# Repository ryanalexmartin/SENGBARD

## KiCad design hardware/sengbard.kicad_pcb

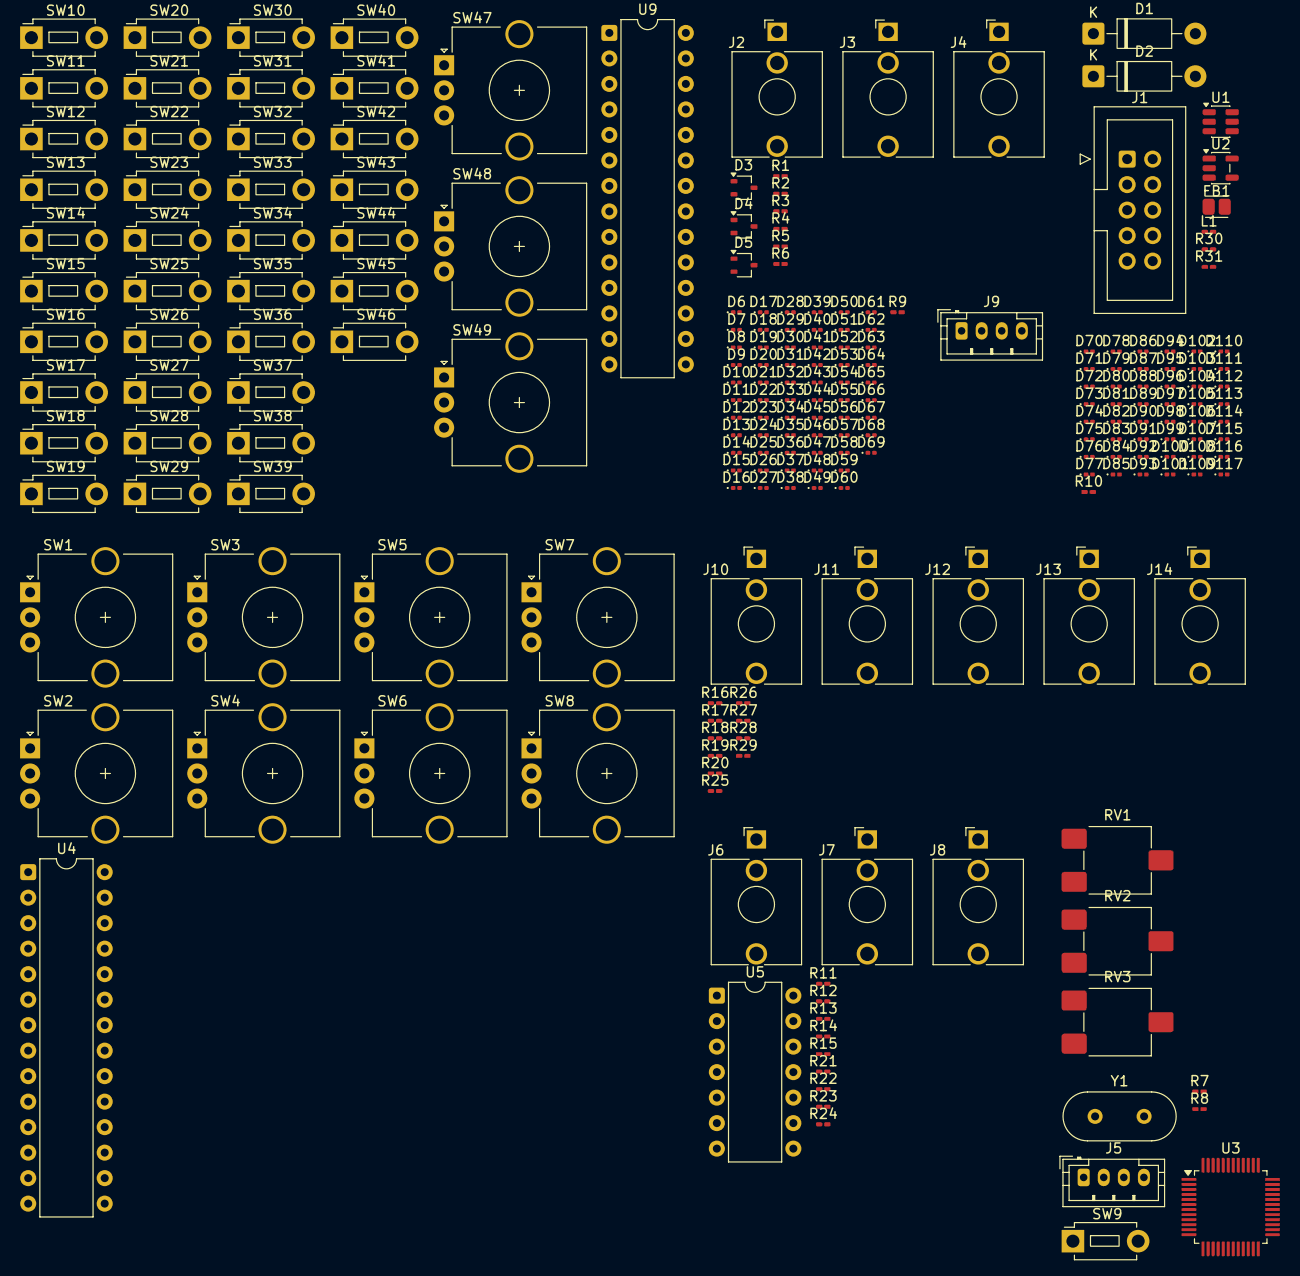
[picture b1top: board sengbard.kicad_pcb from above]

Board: 2 copper layers, 223 parts (0 on the bottom side), 113 nets, no tracks yet.

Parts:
D1, D2: 1N4001; D_DO-41_SOD81_P10.16mm_Horizontal
D3, D4, D5: BAT54W; SOT-323_SC-70
D6, D7, D8, D9, D10, D11, D12, D13, D14, D15, D16, D17, D18, D19, D20, D21, D22, D23, D24, D25, D26, D27, D28, D29, D30, D31, D32, D33, D34, D35, D36, D37, D38, D39, D40, D41, D42, D43, D44, D45, D46, D47, D48, D49, D50, D51, D52, D53, D54, D55, D56, D57, D58, D59, D60, D61, D62, D63, D64, D65, D66, D67, D68, D69, D70, D71, D72, D73, D74, D75, D76, D77, D78, D79, D80, D81, D82, D83, D84, D85, D86, D87, D88, D89, D90, D91, D92, D93, D94, D95, D96, D97, D98, D99, D100, D101, D102, D103, D104, D105, D106, D107, D108, D109, D110, D111, D112, D113, D114, D115, D116, D117: LED; LED_0201_0603Metric
FB1: FerriteBead; L_Eaton_MCL2012V1
J1: Conn_02x05_Odd_Even; IDC-Header_2x05_P2.54mm_Vertical
J2: CLK_IN; Jack_3.5mm_QingPu_WQP-PJ398SM_Vertical_CircularHoles
J3: RST_IN; Jack_3.5mm_QingPu_WQP-PJ398SM_Vertical_CircularHoles
J4: SCENE_CV; Jack_3.5mm_QingPu_WQP-PJ398SM_Vertical_CircularHoles
J5: Conn_01x04; JST_PH_B4B-PH-K_1x04_P2.00mm_Vertical
J6: CV_OUT_T1; Jack_3.5mm_QingPu_WQP-PJ398SM_Vertical_CircularHoles
J7: CV_OUT_T3; Jack_3.5mm_QingPu_WQP-PJ398SM_Vertical_CircularHoles
J8: CV_OUT_T2; Jack_3.5mm_QingPu_WQP-PJ398SM_Vertical_CircularHoles
J9: OLED; JST_PH_B4B-PH-K_1x04_P2.00mm_Vertical
J10: GATE_T1; Jack_3.5mm_QingPu_WQP-PJ398SM_Vertical_CircularHoles
J11: GATE_T2; Jack_3.5mm_QingPu_WQP-PJ398SM_Vertical_CircularHoles
J12: GATE_T3; Jack_3.5mm_QingPu_WQP-PJ398SM_Vertical_CircularHoles
J13: CLK_OUT; Jack_3.5mm_QingPu_WQP-PJ398SM_Vertical_CircularHoles
J14: RST_OUT; Jack_3.5mm_QingPu_WQP-PJ398SM_Vertical_CircularHoles
L1: 10uH; L_0201_0603Metric_Pad0.64x0.40mm_HandSolder
R1, R2, R3, R31: 100k; R_0201_0603Metric_Pad0.64x0.40mm_HandSolder
R4, R5, R6: 47k; R_0201_0603Metric_Pad0.64x0.40mm_HandSolder
R7, R8, R11, R12, R13: 10k; R_0201_0603Metric_Pad0.64x0.40mm_HandSolder
R9, R10: 27k; R_0201_0603Metric_Pad0.64x0.40mm_HandSolder
R14, R15, R21: 20k; R_0201_0603Metric_Pad0.64x0.40mm_HandSolder
R16, R17, R19, R22, R23, R24, R26, R29: 100R; R_0201_0603Metric_Pad0.64x0.40mm_HandSolder
R18, R20, R25, R27, R28: 4.7k; R_0201_0603Metric_Pad0.64x0.40mm_HandSolder
R30: 24.9k; R_0201_0603Metric_Pad0.64x0.40mm_HandSolder
RV1, RV2, RV3: 10k; Potentiometer_ACP_CA6-VSMD_Vertical
SW1, SW2, SW3, SW4, SW5, SW6, SW7, SW8, SW47, SW48, SW49: RotaryEncoder; RotaryEncoder_Alps_EC12E_Vertical_H20mm_CircularMountingHol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
SW9, SW10, SW11, SW12, SW13, SW14, SW15, SW16, SW17, SW18, SW19, SW20, SW21, SW22, SW23, SW24, SW25, SW26, SW27, SW28, SW29, SW30, SW31, SW32, SW33, SW34, SW35, SW36, SW37, SW38, SW39, SW40, SW41, SW42, SW43, SW44, SW45, SW46: SW_Push; SW_PUSH_1P1T_6x3.5mm_H5.0_APEM_MJTP1250
U1: TPS54202DDC; SOT-23-6
U2: AP2112K-3.3; SOT-23-5
U3: STM32G431C6Tx; LQFP-48_7x7mm_P0.5mm
U4, U9: MCP23017_SP; DIP-28_W7.62mm
U5: Opamp_Quad; DIP-14_W7.62mm
Y1: 8MHz; Crystal_HC49-4H_Vertical

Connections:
+3V3: D3.1 (A), D4.1 (A), D5.1 (A), J5.1, J9.3, R7.1, RV1.1, RV2.1, RV3.1, U2.5 (VOUT), U3.1 (VBAT), U3.20 (VREF+), U3.21 (VDDA), U3.24 (VDD), U3.36 (VDD), U3.48 (VDD), U4.9 (VDD), U4.18 (~RESET), U9.9 (VDD), U9.15 (A0), U9.18 (~RESET)
+5V: L1.2, R18.2, R20.2, R25.2, R27.2, R28.2, R31.1, U2.1 (VIN), U2.3 (EN)
+12V: D1.1 (K), U1.3 (VIN), U1.5 (EN), U5.4 (V+)
-12V: D2.2 (A), U5.11 (V-)
-12V_IN: D2.1 (K), J1.1, J1.2
/Buttons/BTN_INT: U9.19 (INTB), U9.20 (INTA)
/Buttons/I2C_SCL: J9.2, U3.43 (PB6), U4.12 (SCK), U9.12 (SCK)
/Buttons/I2C_SDA: J9.1, U3.44 (PB7), U4.13 (SDA), U9.13 (SDA)
/CV Inputs/CLK_IN: D3.3 (K), R1.2, R4.1, U3.9 (PA1)
/CV Inputs/RST_IN: D4.3 (K), R2.2, R5.1, U3.10 (PA2)
/CV Inputs/SCENE_CV_IN: D5.3 (K), R3.2, R6.1, U3.11 (PA3)
/DAC & CV Outputs/STM_DAC_CV1: U3.12 (PA4), U5.3 (+)
/DAC & CV Outputs/STM_DAC_CV2: U3.13 (PA5), U5.5 (+)
/DAC & CV Outputs/STM_DAC_CV3: U3.17 (PB1), U5.10 (+)
/Encoders/MCP_INT: U3.8 (PA0), U4.19 (INTB), U4.20 (INTA)
/MCU - STM32G431/ADC_BPM: RV1.2, U3.31 (PA9)
/MCU - STM32G431/ADC_PW: RV3.2, U3.33 (PA11)
/MCU - STM32G431/ADC_SWG: RV2.2, U3.32 (PA10)
/MCU - STM32G431/NRST: R7.2, SW9.1, U3.7 (PG10)
/MCU - STM32G431/SWCLK: J5.3, U3.38 (PA14)
/MCU - STM32G431/SWDIO: J5.2, U3.37 (PA13)
GND: FB1.1, J2.S, J3.S, J4.S, J5.4, J6.T, J7.T, J8.T, J9.4, J10.S, J11.S, J12.S, J13.S, J14.S, R4.2, R5.2, R6.2, R8.1, R9.1, R10.1, R11.2, R12.2, R13.2, R30.2, RV1.3, RV2.3, RV3.3, SW1.C, SW2.C, SW3.C, SW4.C, SW5.C, SW6.C, SW7.C, SW8.C, SW9.2, U1.1 (GND), U2.2 (GND), U3.19 (VSSA), U3.23 (VSS), U3.35 (VSS), U3.47 (VSS), U4.10 (VSS), U4.15 (A0), U4.16 (A1), U4.17 (A2), U9.10 (VSS), U9.16 (A1), U9.17 (A2)
GND_IN: FB1.2, J1.3, J1.4, J1.5, J1.6, J1.7, J1.8
unnamed: D1.2 (A), J1.10
unnamed: D6.2 (A), D7.2 (A), D8.2 (A), D9.2 (A), D10.2 (A), D11.2 (A), D12.2 (A), D13.2 (A)
unnamed: D10.1 (K), D18.1 (K), D26.1 (K), D34.1 (K), D42.1 (K), D50.1 (K), D58.1 (K), D66.1 (K)
unnamed: D11.1 (K), D19.1 (K), D27.1 (K), D35.1 (K), D43.1 (K), D51.1 (K), D59.1 (K), D67.1 (K)
unnamed: D12.1 (K), D20.1 (K), D28.1 (K), D36.1 (K), D44.1 (K), D52.1 (K), D60.1 (K), D68.1 (K)
unnamed: D13.1 (K), D21.1 (K), D29.1 (K), D37.1 (K), D45.1 (K), D53.1 (K), D61.1 (K), D69.1 (K)
unnamed: D14.2 (A), D15.2 (A), D16.2 (A), D17.2 (A), D18.2 (A), D19.2 (A), D20.2 (A), D21.2 (A)
unnamed: D6.1 (K), D14.1 (K), D22.1 (K), D30.1 (K), D38.1 (K), D46.1 (K), D54.1 (K), D62.1 (K)
unnamed: D7.1 (K), D15.1 (K), D23.1 (K), D31.1 (K), D39.1 (K), D47.1 (K), D55.1 (K), D63.1 (K)
unnamed: D8.1 (K), D16.1 (K), D24.1 (K), D32.1 (K), D40.1 (K), D48.1 (K), D56.1 (K), D64.1 (K)
unnamed: D9.1 (K), D17.1 (K), D25.1 (K), D33.1 (K), D41.1 (K), D49.1 (K), D57.1 (K), D65.1 (K)
unnamed: D22.2 (A), D23.2 (A), D24.2 (A), D25.2 (A), D26.2 (A), D27.2 (A), D28.2 (A), D29.2 (A)
unnamed: D30.2 (A), D31.2 (A), D32.2 (A), D33.2 (A), D34.2 (A), D35.2 (A), D36.2 (A), D37.2 (A)
unnamed: D38.2 (A), D39.2 (A), D40.2 (A), D41.2 (A), D42.2 (A), D43.2 (A), D44.2 (A), D45.2 (A)
unnamed: D46.2 (A), D47.2 (A), D48.2 (A), D49.2 (A), D50.2 (A), D51.2 (A), D52.2 (A), D53.2 (A)
unnamed: D54.2 (A), D55.2 (A), D56.2 (A), D57.2 (A), D58.2 (A), D59.2 (A), D60.2 (A), D61.2 (A)
unnamed: D62.2 (A), D63.2 (A), D64.2 (A), D65.2 (A), D66.2 (A), D67.2 (A), D68.2 (A), D69.2 (A)
unnamed: D70.2 (A), D71.2 (A), D72.2 (A), D73.2 (A), D74.2 (A), D75.2 (A)
unnamed: D76.2 (A), D77.2 (A), D78.2 (A), D79.2 (A), D80.2 (A), D81.2 (A)
unnamed: D82.2 (A), D83.2 (A), D84.2 (A), D85.2 (A), D86.2 (A), D87.2 (A)
unnamed: D88.2 (A), D89.2 (A), D90.2 (A), D91.2 (A), D92.2 (A), D93.2 (A)
unnamed: D94.2 (A), D95.2 (A), D96.2 (A), D97.2 (A), D98.2 (A), D99.2 (A)
unnamed: D100.2 (A), D101.2 (A), D102.2 (A), D103.2 (A), D104.2 (A), D105.2 (A)
unnamed: D70.1 (K), D76.1 (K), D82.1 (K), D88.1 (K), D94.1 (K), D100.1 (K), D106.1 (K), D112.1 (K)
unnamed: D71.1 (K), D77.1 (K), D83.1 (K), D89.1 (K), D95.1 (K), D101.1 (K), D107.1 (K), D113.1 (K)
unnamed: D72.1 (K), D78.1 (K), D84.1 (K), D90.1 (K), D96.1 (K), D102.1 (K), D108.1 (K), D114.1 (K)
unnamed: D73.1 (K), D79.1 (K), D85.1 (K), D91.1 (K), D97.1 (K), D103.1 (K), D109.1 (K), D115.1 (K)
unnamed: D74.1 (K), D80.1 (K), D86.1 (K), D92.1 (K), D98.1 (K), D104.1 (K), D110.1 (K), D116.1 (K)
unnamed: D75.1 (K), D81.1 (K), D87.1 (K), D93.1 (K), D99.1 (K), D105.1 (K), D111.1 (K), D117.1 (K)
unnamed: D106.2 (A), D107.2 (A), D108.2 (A), D109.2 (A), D110.2 (A), D111.2 (A)
unnamed: D112.2 (A), D113.2 (A), D114.2 (A), D115.2 (A), D116.2 (A), D117.2 (A)
unnamed: J2.T, R1.1
unnamed: J3.T, R2.1
unnamed: J4.T, R3.1
unnamed: J6.S, R22.2
unnamed: J7.S, R23.2
unnamed: J8.S, R24.2
unnamed: J10.T, R16.2
unnamed: J11.T, R17.2
unnamed: J12.T, R19.2
unnamed: J13.T, R26.2
unnamed: J14.T, R29.2
unnamed: R14.2, R22.1, U5.1
unnamed: R15.2, R23.1, U5.8
unnamed: R21.2, R24.1, U5.7
unnamed: R30.1, R31.2, U1.4 (FB)
unnamed: L1.1, U1.2 (SW)
unnamed: R8.2, U3.45 (PB8)
unnamed: U3.5 (PF0), Y1.2
unnamed: U3.6 (PF1), Y1.1
unnamed: SW5.A, U4.21 (GPA0)
unnamed: SW5.B, U4.22 (GPA1)
unnamed: SW6.A, U4.23 (GPA2)
unnamed: SW6.B, U4.24 (GPA3)
unnamed: SW7.A, U4.25 (GPA4)
unnamed: SW7.B, U4.26 (GPA5)
unnamed: SW8.A, U4.27 (GPA6)
unnamed: SW8.B, U4.28 (GPA7)
unnamed: SW1.A, U4.1 (GPB0)
unnamed: SW1.B, U4.2 (GPB1)
unnamed: SW2.A, U4.3 (GPB2)
unnamed: SW2.B, U4.4 (GPB3)
unnamed: SW3.A, U4.5 (GPB4)
unnamed: SW3.B, U4.6 (GPB5)
unnamed: SW4.A, U4.7 (GPB6)
unnamed: SW4.B, U4.8 (GPB7)
unnamed: R11.1, R14.1, U5.2 (-)
unnamed: R12.1, R21.1, U5.6 (-)
unnamed: R13.1, R15.1, U5.9 (-)
unnamed: R16.1, R18.1
unnamed: R17.1, R20.1
unnamed: R19.1, R25.1
unnamed: R26.1, R27.1
unnamed: R28.1, R29.1
unnamed: SW10.1, SW18.1, SW26.1, SW34.1, SW42.1, SW47.A, U9.21 (GPA0)
unnamed: SW11.1, SW19.1, SW27.1, SW35.1, SW43.1, SW47.B, U9.22 (GPA1)
unnamed: SW12.1, SW20.1, SW28.1, SW36.1, SW44.1, SW48.A, U9.23 (GPA2)
unnamed: SW13.1, SW21.1, SW29.1, SW37.1, SW45.1, SW48.B, U9.24 (GPA3)
unnamed: SW14.1, SW22.1, SW30.1, SW38.1, SW46.1, SW49.A, U9.25 (GPA4)
unnamed: SW15.1, SW23.1, SW31.1, SW39.1, SW49.B, U9.26 (GPA5)
unnamed: SW16.1, SW24.1, SW32.1, SW40.1, U9.27 (GPA6)
unnamed: SW17.1, SW25.1, SW33.1, SW41.1, U9.28 (GPA7)
unnamed: SW10.2, SW11.2, SW12.2, SW13.2, SW14.2, SW15.2, SW16.2, SW17.2, U9.1 (GPB0)
unnamed: SW18.2, SW19.2, SW20.2, SW21.2, SW22.2, SW23.2, SW24.2, SW25.2, U9.2 (GPB1)
unnamed: SW26.2, SW27.2, SW28.2, SW29.2, SW30.2, SW31.2, SW32.2, SW33.2, U9.3 (GPB2)
unnamed: SW34.2, SW35.2, SW36.2, SW37.2, SW38.2, SW39.2, SW40.2, SW41.2, U9.4 (GPB3)
unnamed: SW42.2, SW43.2, SW44.2, SW45.2, SW46.2, U9.5 (GPB4)
unnamed: SW47.C, U9.6 (GPB5)
unnamed: SW48.C, U9.7 (GPB6)
unnamed: SW49.C, U9.8 (GPB7)

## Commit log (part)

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2026-01-27 Remove KiCad autosave files
2026-01-27 Add KiCad temp files to gitignore
